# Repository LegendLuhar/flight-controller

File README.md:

# Flight Controller PCB

Custom STM32G474-based flight controller PCB and firmware project focused on embedded systems, hardware design, and real-time firmware development.

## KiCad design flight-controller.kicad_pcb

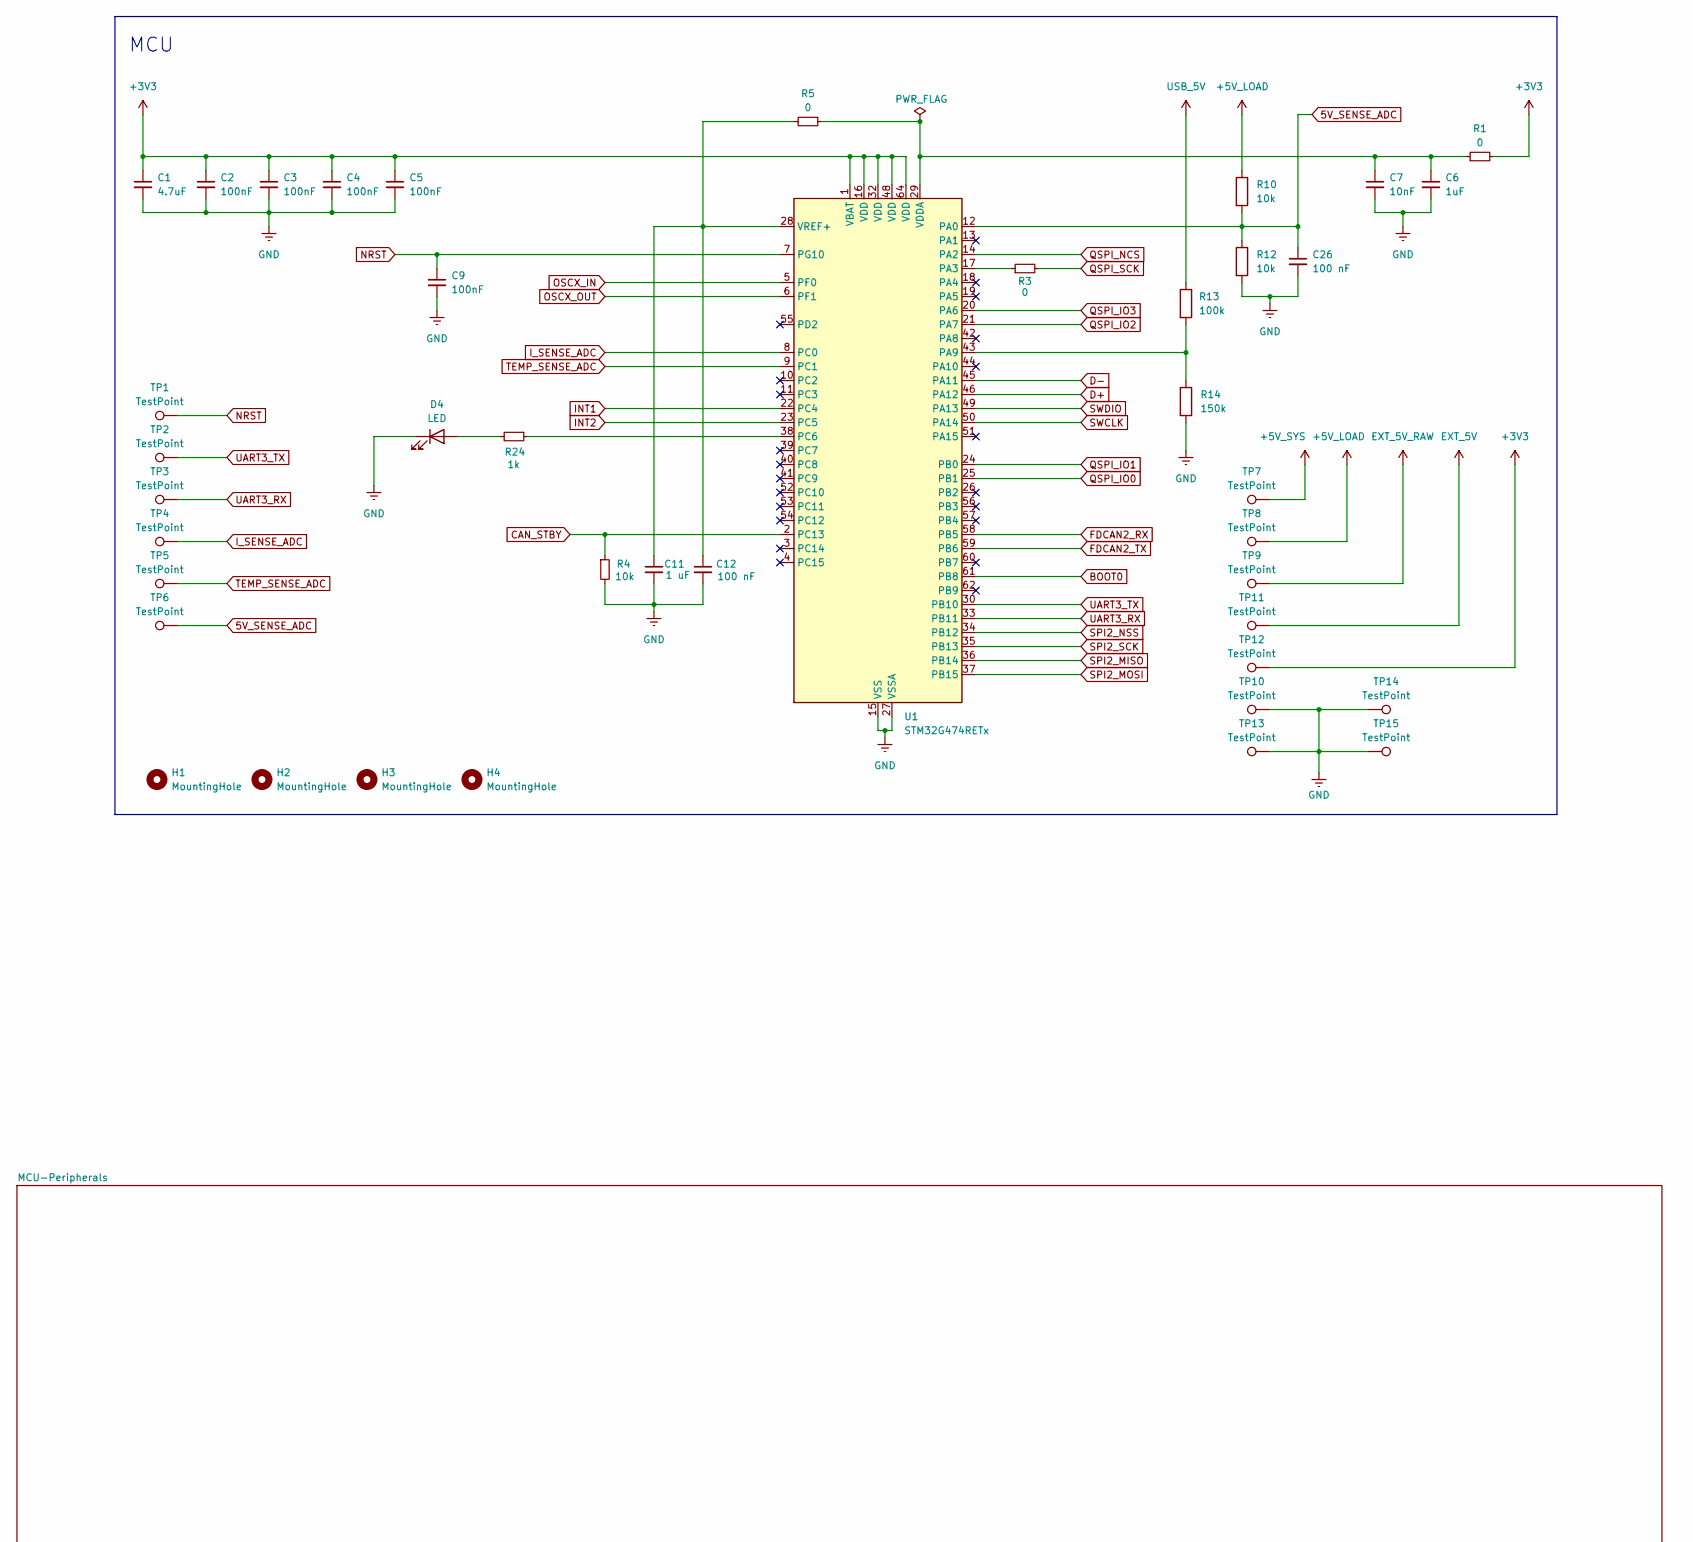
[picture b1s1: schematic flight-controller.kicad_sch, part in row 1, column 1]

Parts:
C1: 4.7uF; C_0805_2012Metric
C2, C3, C4, C5, C9: 100nF; C_0603_1608Metric
C6: 1uF; C_0603_1608Metric
C7: 10nF; C_0603_1608Metric
C11: 1 uF; C_0603_1608Metric
C12, C26: 100 nF; C_0603_1608Metric
D4: LED; LED_0603_1608Metric
H1, H2, H3, H4: MountingHole; MountingHole_3.2mm_M3_Pad_Via
R1, R3, R5: 0; R_0603_1608Metric
R4, R10, R12: 10k; R_0603_1608Metric
R13: 100k; R_0603_1608Metric
R14: 150k; R_0603_1608Metric
R24: 1k; R_0603_1608Metric
TP1, TP2, TP3, TP4, TP5, TP6, TP7, TP8, TP9, TP10, TP11, TP12, TP13, TP14, TP15: TestPoint; TestPoint_Pad_D1.0mm
U1: STM32G474RETx; LQFP-64_10x10mm_P0.5mm

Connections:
5V_SENSE_ADC: C26.1, R10.2, R12.1, TP6.1 (1_1), U1.12 (PA0)
+3V3: C1.1, C2.1, C3.1, C4.1, C5.1, R1.2, TP12.1 (1_1), U1.1 (VBAT), U1.16 (VDD), U1.32 (VDD), U1.48 (VDD), U1.64 (VDD); also elsewhere on the board
+5V_LOAD: R10.1, TP8.1 (1_1); also elsewhere on the board
+5V_SYS: TP7.1 (1_1); also elsewhere on the board
BOOT0: U1.61 (PB8); also elsewhere on the board
CAN_STBY: R4.1, U1.2 (PC13); also elsewhere on the board
D+: U1.46 (PA12); also elsewhere on the board
D-: U1.45 (PA11); also elsewhere on the board
EXT_5V: TP11.1 (1_1); also elsewhere on the board
EXT_5V_RAW: TP9.1 (1_1); also elsewhere on the board
FDCAN2_RX: U1.58 (PB5); also elsewhere on the board
FDCAN2_TX: U1.59 (PB6); also elsewhere on the board
GND: C1.2, C2.2, C3.2, C4.2, C5.2, C6.2, C7.2, C9.2, C11.2, C12.2, C26.2, D4.1 (K), R4.2, R12.2, R14.2, TP10.1 (1_1), TP13.1 (1_1), TP14.1 (1_1), TP15.1 (1_1), U1.15 (VSS), U1.27 (VSSA), U1.31 (VSS), U1.47 (VSS), U1.63 (VSS); also elsewhere on the board
INT1: U1.22 (PC4); also elsewhere on the board
INT2: U1.23 (PC5); also elsewhere on the board
I_SENSE_ADC: TP4.1 (1_1), U1.8 (PC0); also elsewhere on the board
NRST: C9.1, TP1.1 (1_1), U1.7 (PG10); also elsewhere on the board
unnamed: D4.2 (A), R24.2
unnamed: R3.1, U1.17 (PA3)
unnamed: R13.2, R14.1, U1.43 (PA9)
unnamed: R24.1, U1.38 (PC6)
unnamed: C6.1, C7.1, R1.1, R5.1, U1.29 (VDDA)
unnamed: C11.1, C12.1, R5.2, U1.28 (VREF+)
OSCX_IN: U1.5 (PF0); also elsewhere on the board
OSCX_OUT: U1.6 (PF1); also elsewhere on the board
QSPI_IO0: U1.25 (PB1); also elsewhere on the board
QSPI_IO1: U1.24 (PB0); also elsewhere on the board
QSPI_IO2: U1.21 (PA7); also elsewhere on the board
QSPI_IO3: U1.20 (PA6); also elsewhere on the board
QSPI_NCS: U1.14 (PA2); also elsewhere on the board
QSPI_SCK: R3.2; also elsewhere on the board
SPI2_MISO: U1.36 (PB14); also elsewhere on the board
SPI2_MOSI: U1.37 (PB15); also elsewhere on the board
SPI2_NSS: U1.34 (PB12); also elsewhere on the board
SPI2_SCK: U1.35 (PB13); also elsewhere on the board
SWCLK: U1.50 (PA14); also elsewhere on the board
SWDIO: U1.49 (PA13); also elsewhere on the board
TEMP_SENSE_ADC: TP5.1 (1_1), U1.9 (PC1); also elsewhere on the board
UART3_RX: TP3.1 (1_1), U1.33 (PB11); also elsewhere on the board
UART3_TX: TP2.1 (1_1), U1.30 (PB10); also elsewhere on the board
USB_5V: R13.1; also elsewhere on the board

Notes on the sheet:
MCU

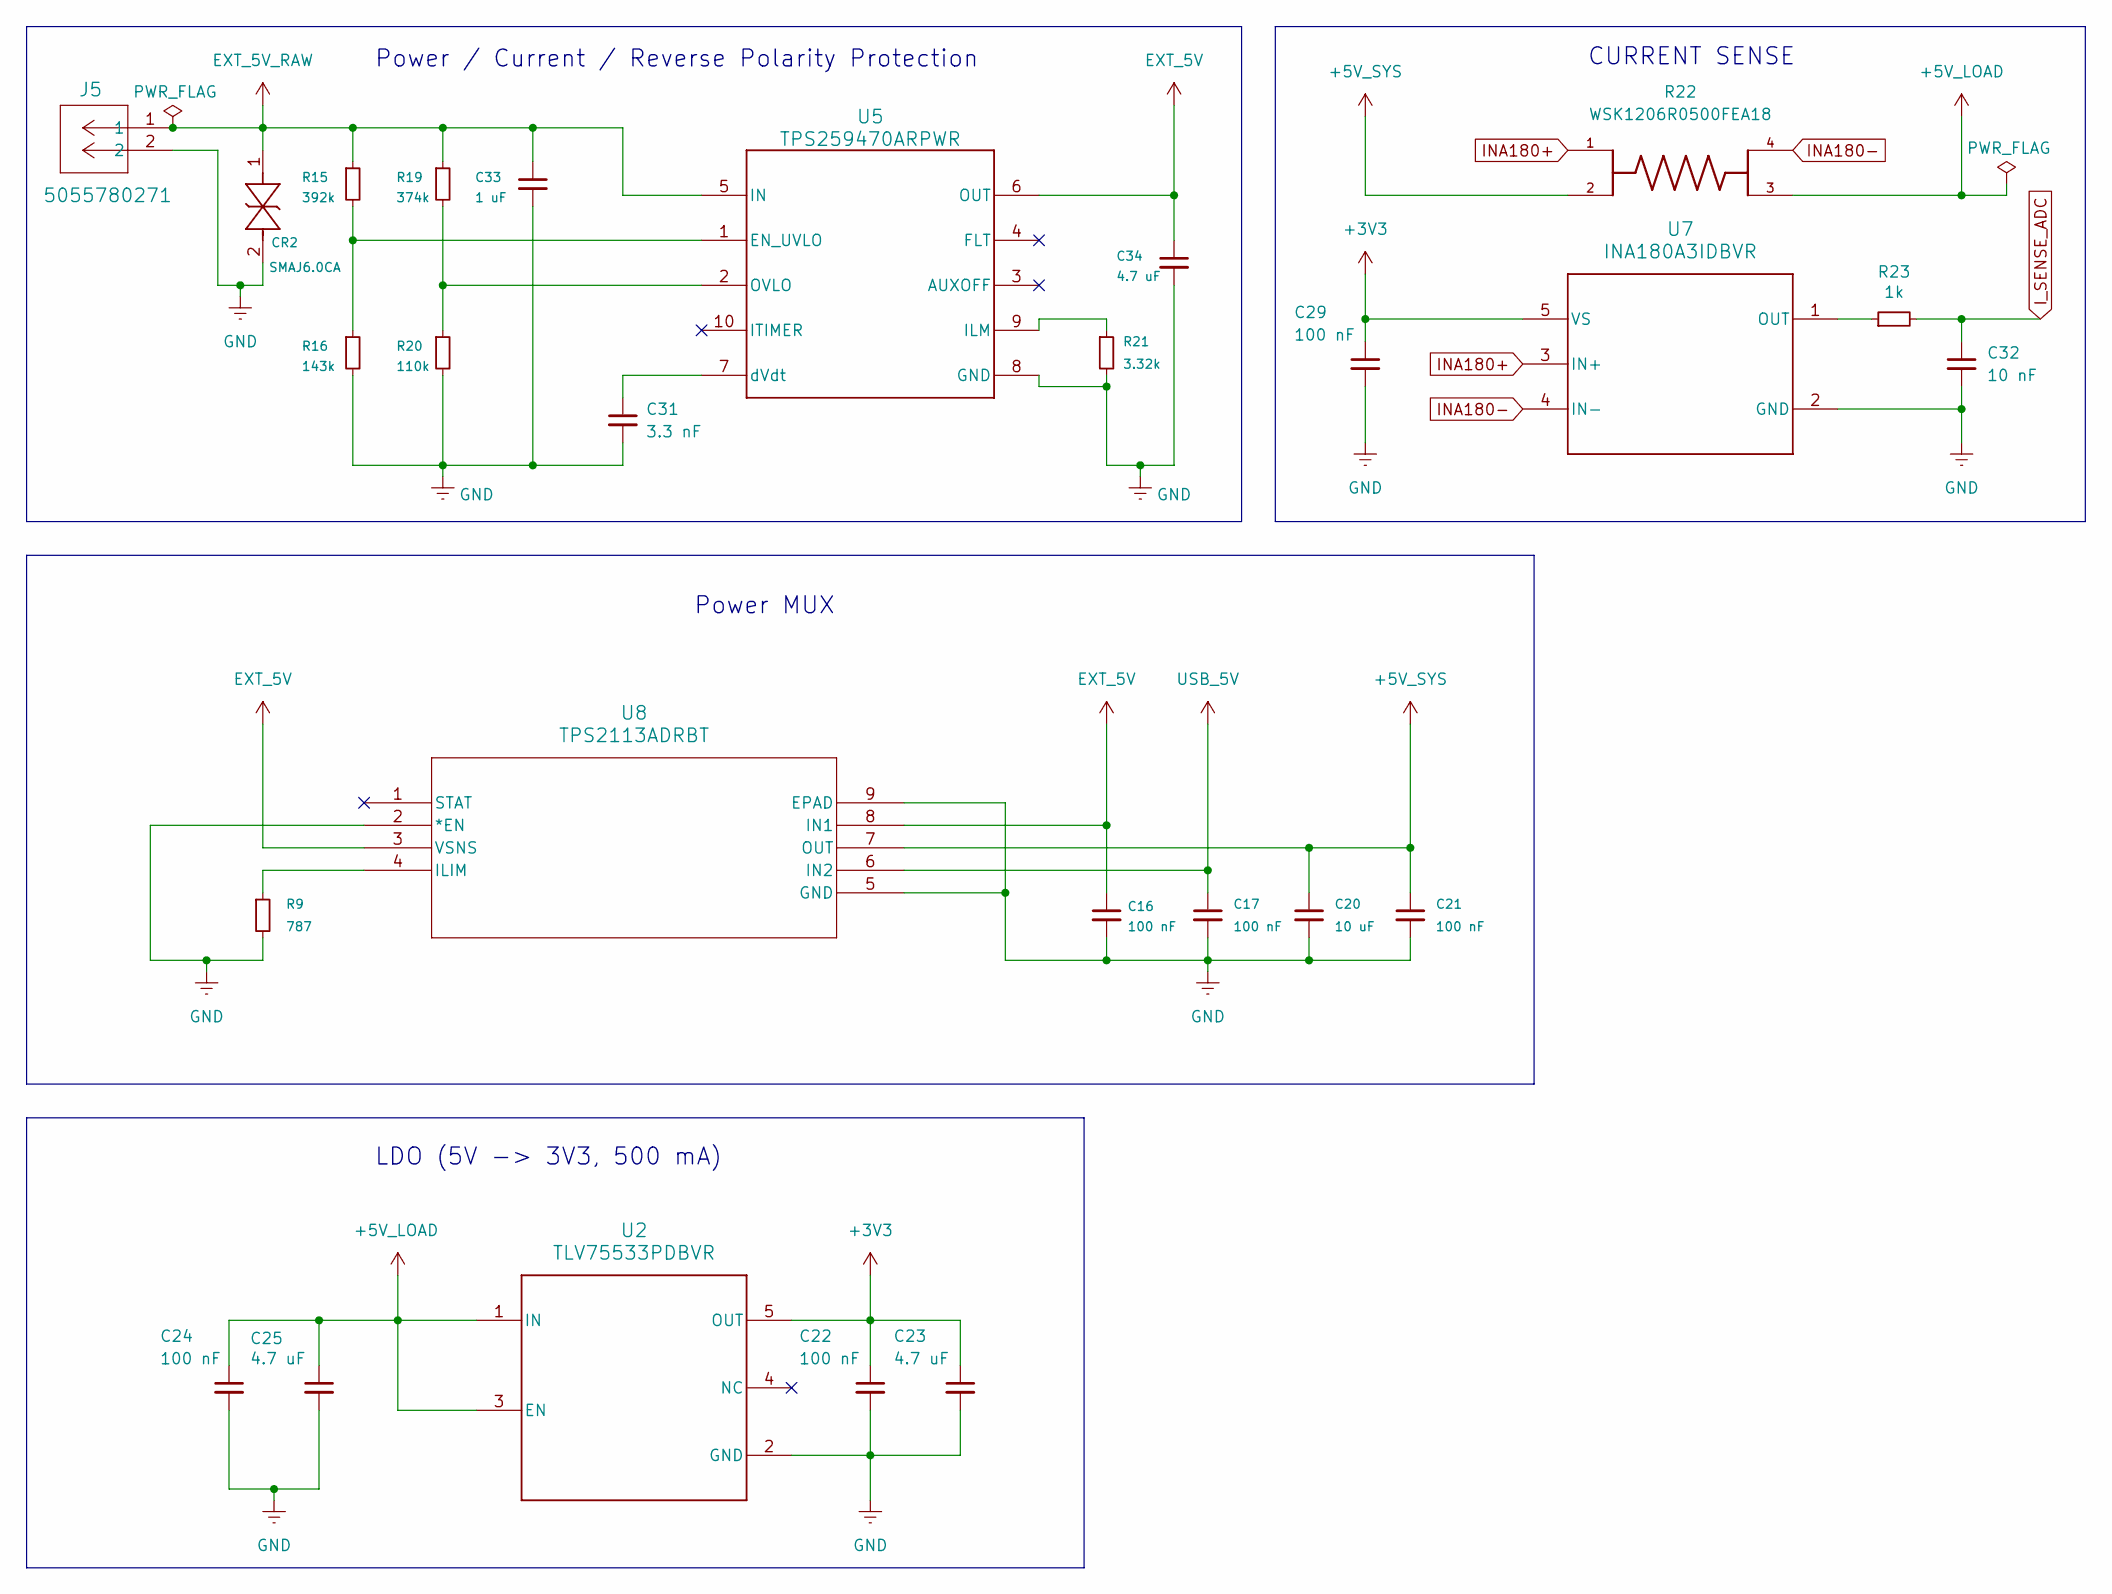
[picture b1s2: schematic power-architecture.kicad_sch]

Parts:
C16, C17, C21, C22, C24, C29: 100 nF; C_0603_1608Metric
C20: 10 uF; C_0603_1608Metric
C23, C25, C34: 4.7 uF; C_0805_2012Metric
C31: 3.3 nF; C_0603_1608Metric
C32: 10 nF; C_0603_1608Metric
C33: 1 uF; C_0603_1608Metric
CR2: SMAJ6.0CA; SMASeries_LTF
J5: 5055780271; CONN_505578_02_MOL
R9: 787; R_0603_1608Metric
R15: 392k; R_0603_1608Metric
R16: 143k; R_0603_1608Metric
R19: 374k; R_0603_1608Metric
R20: 110k; R_0603_1608Metric
R21: 3.32k; R_0603_1608Metric
R22: WSK1206R0500FEA18; RES_WSK1206R0500FEA18; PARTREV 26-Jul-2023
R23: 1k; R_0603_1608Metric
U2: TLV75533PDBVR; DBV0005A_L
U5: TPS259470ARPWR; RPW0010A-MFG
U7: INA180A3IDBVR; DBV0005A_L
U8: TPS2113ADRBT; DRB8_2P4X1P65

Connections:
+3V3: C22.1, C23.1, C29.1, U2.5 (OUT), U7.5 (VS); also elsewhere on the board
+5V_LOAD: C24.1, C25.1, R22.3, U2.1 (IN), U2.3 (EN); also elsewhere on the board
+5V_SYS: C20.1, C21.1, R22.2, U8.7 (OUT); also elsewhere on the board
EXT_5V: C16.1, C34.1, U5.6 (OUT), U8.3 (VSNS), U8.8 (IN1); also elsewhere on the board
EXT_5V_RAW: C33.1, CR2.1, J5.1, R15.1, R19.1, U5.5 (IN); also elsewhere on the board
GND: C16.2, C17.2, C20.2, C21.2, C22.2, C23.2, C24.2, C25.2, C29.2, C31.2, C32.2, C33.2, C34.2, CR2.2, J5.2, R9.2, R16.2, R20.2, R21.2, U2.2 (GND), U5.8 (GND), U7.2 (GND), U8.2 (*EN), U8.5 (GND), U8.9 (EPAD); also elsewhere on the board
INA180+: R22.1, U7.3 (IN+)
INA180-: R22.4, U7.4 (IN-)
I_SENSE_ADC: C32.1, R23.2; also elsewhere on the board
unnamed: R15.2, R16.1, U5.1 (EN_UVLO)
unnamed: R21.1, U5.9 (ILM)
unnamed: R19.2, R20.1, U5.2 (OVLO)
unnamed: C31.1, U5.7 (dVdt)
unnamed: R23.1, U7.1 (OUT)
unnamed: R9.1, U8.4 (ILIM)
USB_5V: C17.1, U8.6 (IN2); also elsewhere on the board

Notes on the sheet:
LDO (5V -> 3V3, 500 mA)
Power MUX
CURRENT SENSE
Power / Current / Reverse Polarity Protection

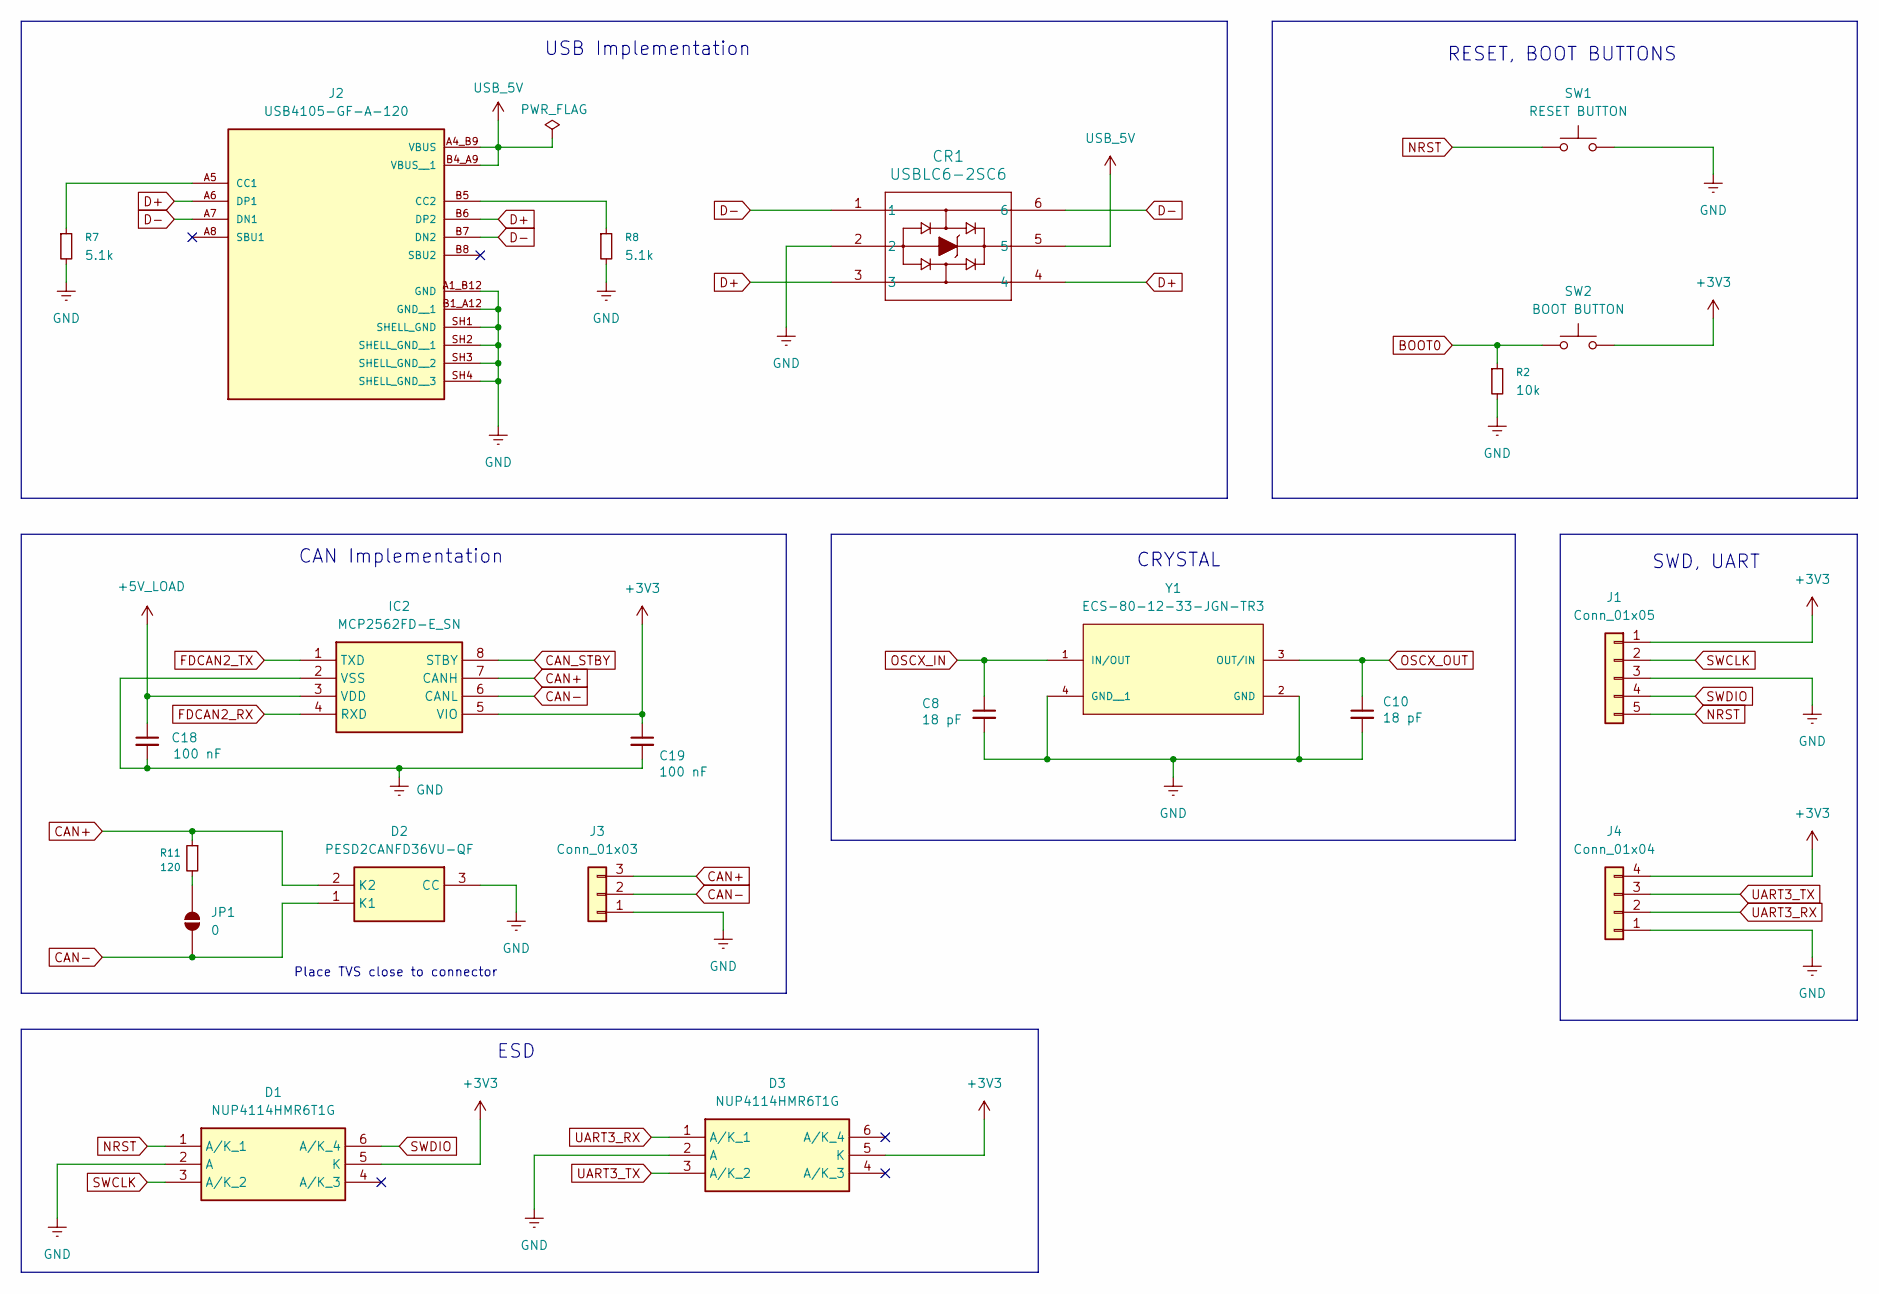
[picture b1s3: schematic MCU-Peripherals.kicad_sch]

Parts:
C8, C10: 18 pF; C_0603_1608Metric
C18, C19: 100 nF; C_0603_1608Metric
CR1: USBLC6-2SC6; SOT23-6L_STM
D1, D3: NUP4114HMR6T1G; SOT95P275X110-6N; Mouser Part Number 863-NUP4114HMR6T1G
D2: PESD2CANFD36VU-QF; PESD2CANFD36VUQF; Mouser Part Number 771-PESD2CANFD36VUQF
IC2: MCP2562FD-E_SN; SOIC127P600X175-8N; Mouser Part Number 579-MCP2562FD-E/SN
J1: Conn_01x05; JST_GH_SM05B-GHS-TB_1x05-1MP_P1.25mm_Horizontal
J2: USB4105-GF-A-120; GCT_USB4105-GF-A-120; PARTREV B3
J3: Conn_01x03; JST_GH_SM03B-GHS-TB_1x03-1MP_P1.25mm_Horizontal
J4: Conn_01x04; JST_GH_SM04B-GHS-TB_1x04-1MP_P1.25mm_Horizontal
JP1: 0; R_0603_1608Metric
R2: 10k; R_0603_1608Metric
R7, R8: 5.1k; R_0603_1608Metric
R11: 120; R_0603_1608Metric
SW1: RESET BUTTON; SW_SPST_SKQG_WithStem
SW2: BOOT BUTTON; SW_SPST_SKQG_WithStem
Y1: ECS-80-12-33-JGN-TR3; XTAL_ECS-240-8-33-AGN-TR

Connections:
+3V3: C19.1, D1.5 (K), D3.5 (K), IC2.5 (VIO), J1.1, J4.4, SW2.2; also elsewhere on the board
+5V_LOAD: C18.1, IC2.3 (VDD); also elsewhere on the board
BOOT0: R2.1, SW2.1; also elsewhere on the board
CAN+: D2.2 (K2), IC2.7 (CANH), J3.3, R11.1
CAN-: D2.1 (K1), IC2.6 (CANL), J3.2, JP1.1 (A)
CAN_STBY: IC2.8 (STBY); also elsewhere on the board
D+: CR1.3, CR1.4, J2.A6 (DP1), J2.B6 (DP2); also elsewhere on the board
D-: CR1.1, CR1.6, J2.A7 (DN1), J2.B7 (DN2); also elsewhere on the board
FDCAN2_RX: IC2.4 (RXD); also elsewhere on the board
FDCAN2_TX: IC2.1 (TXD); also elsewhere on the board
GND: C8.2, C10.2, C18.2, C19.2, CR1.2, D1.2 (A), D2.3 (CC), D3.2 (A), IC2.2 (VSS), J1.3, J2.A1_B12 (GND), J2.B1_A12 (GND__1), J2.SH1 (SHELL_GND), J2.SH2 (SHELL_GND__1), J2.SH3 (SHELL_GND__2), J2.SH4 (SHELL_GND__3), J3.1, J4.1, R2.2, R7.2, R8.2, SW1.2, Y1.2 (GND), Y1.4 (GND__1); also elsewhere on the board
NRST: D1.1 (A/K_1), J1.5, SW1.1; also elsewhere on the board
unnamed: J2.A5 (CC1), R7.1
unnamed: J2.B5 (CC2), R8.1
unnamed: JP1.2 (B), R11.2
OSCX_IN: C8.1, Y1.1 (IN/OUT); also elsewhere on the board
OSCX_OUT: C10.1, Y1.3 (OUT/IN); also elsewhere on the board
SWCLK: D1.3 (A/K_2), J1.2; also elsewhere on the board
SWDIO: D1.6 (A/K_4), J1.4; also elsewhere on the board
UART3_RX: D3.1 (A/K_1), J4.2; also elsewhere on the board
UART3_TX: D3.3 (A/K_2), J4.3; also elsewhere on the board
USB_5V: CR1.5, J2.A4_B9 (VBUS), J2.B4_A9 (VBUS__1); also elsewhere on the board

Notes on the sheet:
ESD
RESET, BOOT BUTTONS
CAN Implementation
SWD, UART
USB Implementation
CRYSTAL
Place TVS close to connector

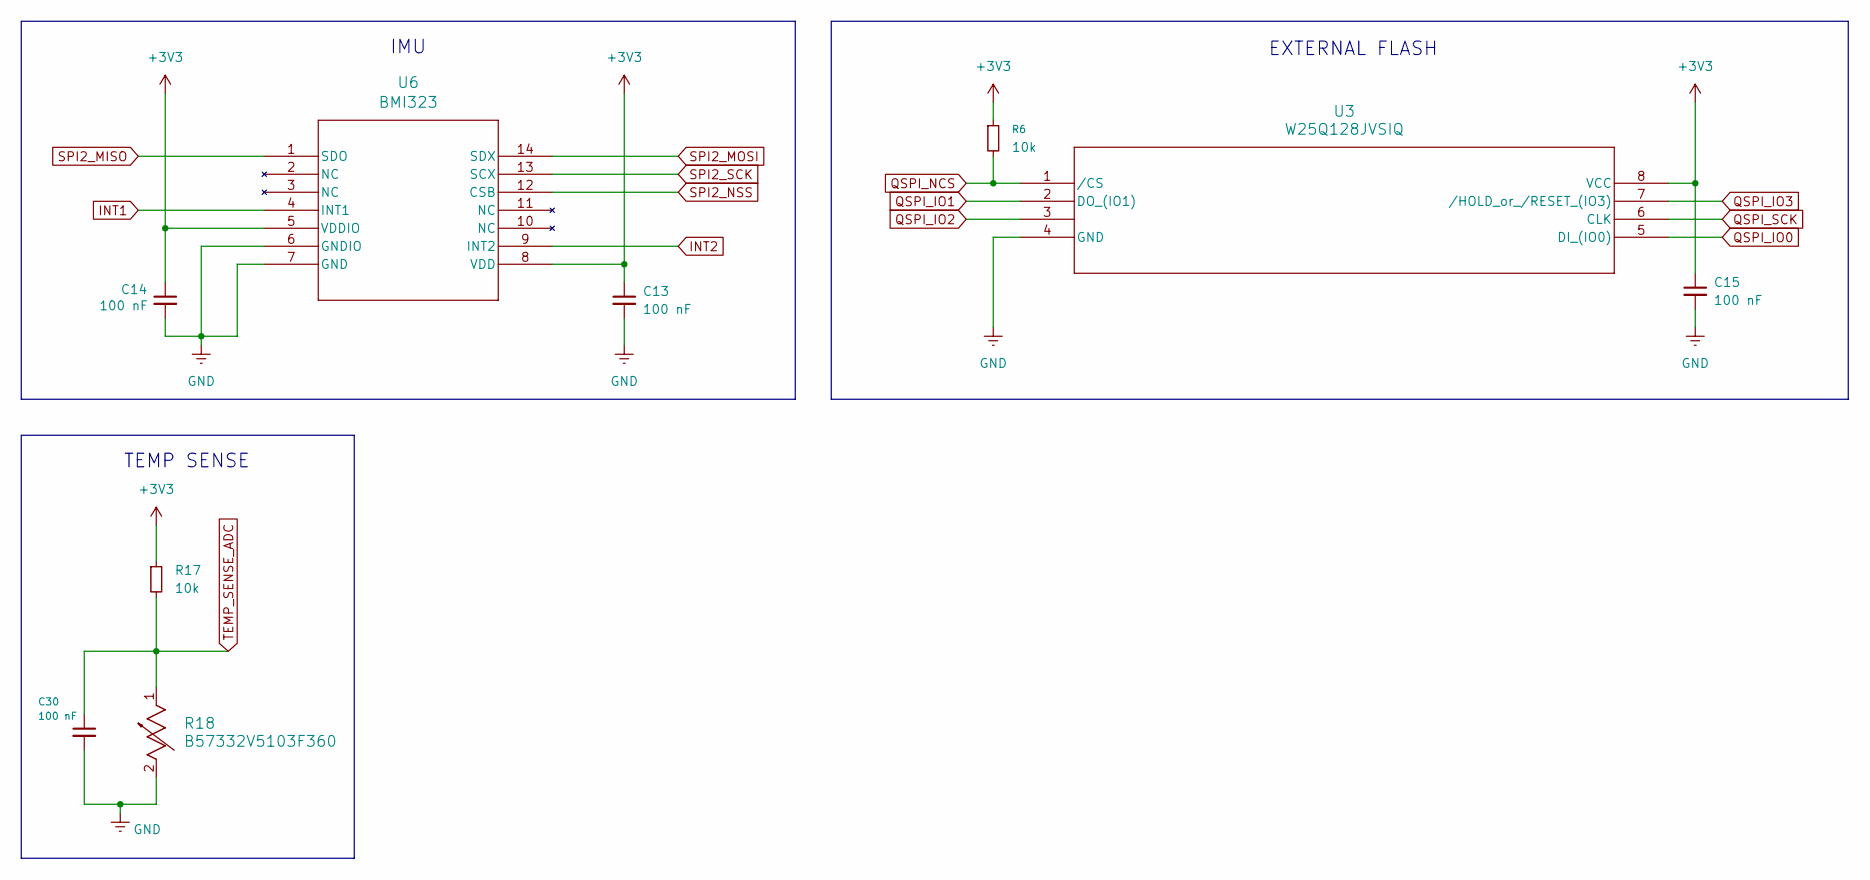
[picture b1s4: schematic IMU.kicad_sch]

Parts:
C13, C14, C15, C30: 100 nF; C_0603_1608Metric
R6, R17: 10k; R_0603_1608Metric
R18: B57332V5103F360; TRES_B57332V5103F360
U3: W25Q128JVSIQ; SOIC_128JVSIQ_WIN
U6: BMI323; BMI323_BOS

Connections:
+3V3: C13.1, C14.1, C15.1, R6.1, R17.1, U3.8 (VCC), U6.5 (VDDIO), U6.8 (VDD); also elsewhere on the board
GND: C13.2, C14.2, C15.2, C30.2, R18.2, U3.4 (GND), U6.6 (GNDIO), U6.7 (GND); also elsewhere on the board
INT1: U6.4 (INT1); also elsewhere on the board
INT2: U6.9 (INT2); also elsewhere on the board
QSPI_IO0: U3.5 (DI_(IO0)); also elsewhere on the board
QSPI_IO1: U3.2 (DO_(IO1)); also elsewhere on the board
QSPI_IO2: U3.3; also elsewhere on the board
QSPI_IO3: U3.7 (/HOLD_or_/RESET_(IO3)); also elsewhere on the board
QSPI_NCS: R6.2, U3.1 (/CS); also elsewhere on the board
QSPI_SCK: U3.6 (CLK); also elsewhere on the board
SPI2_MISO: U6.1 (SDO); also elsewhere on the board
SPI2_MOSI: U6.14 (SDX); also elsewhere on the board
SPI2_NSS: U6.12 (CSB); also elsewhere on the board
SPI2_SCK: U6.13 (SCX); also elsewhere on the board
TEMP_SENSE_ADC: C30.1, R17.2, R18.1; also elsewhere on the board

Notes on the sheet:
TEMP SENSE
IMU
EXTERNAL FLASH

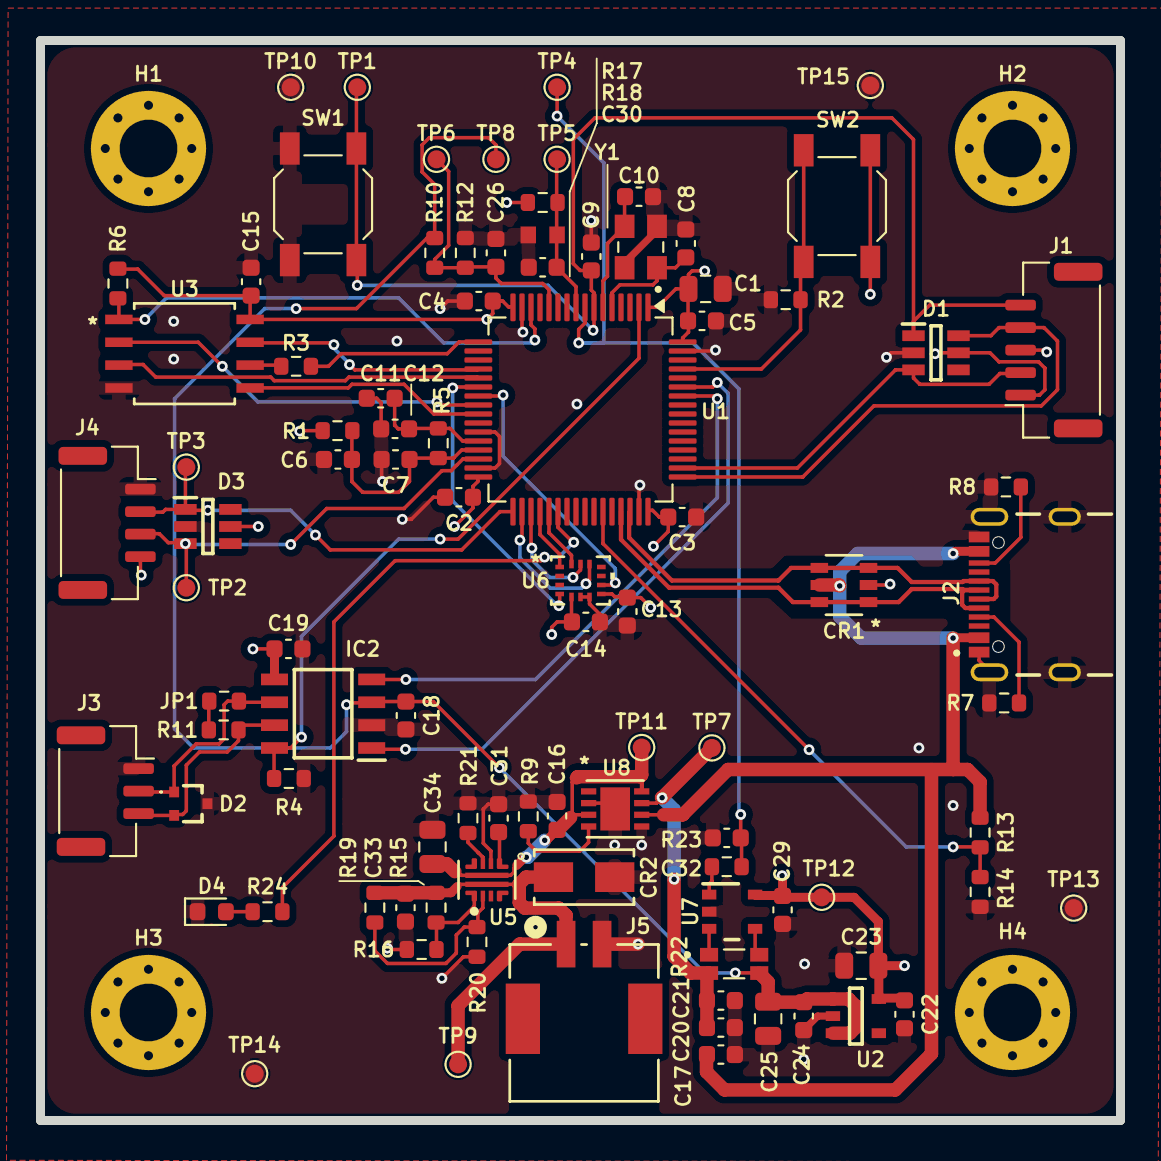
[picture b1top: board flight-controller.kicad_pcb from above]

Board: 4 copper layers, 60.0 x 60.0 mm, 98 parts (0 on the bottom side), 54 nets.
